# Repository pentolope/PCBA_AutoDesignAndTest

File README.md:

# pcbqa — board-agnostic KiCad / JLCPCB verification and release

A fail-closed validator that takes a native KiCad project plus a declarative
manifest and produces a machine-readable pass/fail matrix, generates the
fabrication outputs a release commit carries, and proves that a commit is one a
release tag may name.

**A release is a Git tag.**

- **commit** = the complete project state
- **committed fabrication artifacts** = the exact historical manufacturing
  outputs, kept as ordinary files so an old board can be refabricated years
  later without regenerating anything
- **Git tag** = the release identity
- **toolkit release gates** = engineering proof that the tagged state is
  acceptable

Git already provides immutable history, branches, diffs, rollback and exact
source identity. This toolkit does not reimplement any of that; it answers the
engineering question Git cannot: are these artifacts the ones this design
produces, and does this design pass.

KiCad is the sole design authority: nothing is believed because a report, a
label or a Python model says so. This repository contains no production board —
concrete designs appear only as isolated fixtures and examples.

Consume it from a board repository as a pinned Git submodule at
`tooling/PCBA_AutoDesignAndTest`. It carries one submodule of its own:
KiCad Routing Tools at `tooling/KiCadRoutingTools`, pinned to a commit on its
`pcba-autonomy` branch, so clone recursively.

## Commands

Ubuntu, and the system Python 3: the `kicad` package installs `pcbnew` into
this interpreter's `dist-packages` and `kicad-cli` onto PATH, and Shapely is
`python3-shapely`. See `docs/prerequisites.md`.

```bash
python3 run.py preflight
```
```bash
python3 run.py selftest
```
```bash
python3 run.py build <manifest.json>
```
```bash
python3 run.py validate <manifest.json> --write
```
```bash
python3 run.py check-board <manifest.json>
```
```bash
python3 run.py release-check <manifest.json>
```
```bash
python3 run.py gates
```
```bash
python3 run.py gates --missing <manifest.json>
```
```bash
python3 run.py fab refresh | select | impedance | export-stackup
```

`fab refresh` is the only command that may touch the network. It writes its
acquisition into a scratch directory in the committed catalog layout and
prints the semantic diff. After review, replace
`profiles/jlcpcb/catalog` with that scratch catalog as one exact set; do not
merge evidence directories. The commit is the approval and Git is the history.

`<manifest.json>` is a path. For this repository's own fixtures a bare name also
works — `portability`, `clean`, or a negative fixture's directory name.

`validate --only=` takes exact gate IDs, fnmatch patterns over them
(`ROUTE.*`), or a gate class — `design`, `release-artifact`, `fixture` — and a
partial run is always a diagnostic, never a verdict. The same selection is
available in-process as `pcbqa.gates.evaluate(manifest, only=..., 
board_path=...)`, where `board_path` substitutes a candidate board so a
routing search can be judged by the gates that will judge the release.

`check-board` is the sub-second integrity preflight: the tree's board is the
accepted routing candidate, the committed artifacts match the design as it
stands (naming which closure member moved when not), and no KiCad file the
design does not reach sits beside it. `gates --missing` lists every gate a
manifest has not enabled and the key that would enable it.

A manifest is validated against `schemas/manifest.v2.json` before any command
runs, and a key the toolkit does not implement is refused by name. Board-local
data belongs under `x_`-prefixed keys, permitted at every level;
`description`, `note`, `why` and `rationale` are annotation strings, also
permitted at every level.

## The release workflow

```text
develop on a branch
        ↓  run.py build          regenerate the fabrication outputs into the tree
        ↓  run.py validate -w    judge the design and those exact artifacts
        ↓  git commit            artifacts included; they are ordinary files
        ↓  run.py release-check  clean tree, exact submodules, gates pass now
        ↓  git tag -a            the release exists
```

A branch carries work in progress; a tag over a valid committed state is the
release.

`build` stages the design — the sources the manifest declares, the library
tables, and whatever those name inside the project — and runs KiCad against
that, never against the authoritative files. `pcb drc --refill-zones
--save-board`, which this validator requires because an export ships whatever
zone fill is stored, demonstrably rewrites the board. Every recursively
discovered project input must resolve inside the declared project root before
it can be staged. Outputs are installed into the paths the manifest declares,
all or nothing, together with `fabrication.json`: the digest of every artifact
and the source closure it came from.

`validate` exits nonzero on a blocking result. It is read-only unless `--write`
is given, so ordinary development validation never touches the working tree.

`release-check` writes nothing durable (its scratch run is discarded) and
changes no Git state. It exits zero only when
Git can say the tree is exactly the commit (submodules included), every release
artifact and every piece of required evidence is tracked, every mandatory gate
passes now, and the committed verdict is about this same design. Creating the
tag is a deliberate act and is left to the user.

To re-verify a historical release, check the tag out and run `release-check`
against it: the artifacts, the reports and the verdict are all in that commit,
and nothing has to be regenerated. Prefer annotated tags (`git tag -a`, or
`-s` to sign); protecting them from being moved or deleted is a property of the
remote — GitHub tag-protection rules, or `receive.denyDeleteTag` on a bare
repository — not something a validator can enforce locally.

Scratch for one invocation lives in `out/<board_id>/<run_id>/` and nothing
durable is kept there.

## Layout

| Path | Role |
|---|---|
| `pcbqa/core.py` | statuses, results, manifest, provenance, gate registry, reporting |
| `pcbqa/geom.py` | native pad/mask/via geometry via KiCad's own effective shapes |
| `pcbqa/gerber.py` | independent Gerber X2 + Excellon readers, incl. an aperture-macro interpreter |
| `pcbqa/canonical.py` | checkout-independent digests, driven by `.gitattributes` |
| `pcbqa/closure.py` | the source closure: what a result depends on |
| `pcbqa/claim.py` | one evidence model, and the conservative verdict rule |
| `pcbqa/sim/model_registry.py` | per-phenomenon simulation model evidence and coverage |
| `pcbqa/transmission_line.py` | manufacturer-independent closed forms |
| `pcbqa/build.py` | generating the fabrication outputs and installing them |
| `pcbqa/artifacts.py` | which committed files are the release artifact set |
| `pcbqa/release.py` | the Git preconditions of a release tag |
| `pcbqa/connectivity.py` | copper graph built from geometric intersection |
| `pcbqa/rules/` | reusable rule types: `NetTopologyRule`, `ConnectorContractRule`, `PlacementRule` |
| `pcbqa/gates/` | the gates themselves |
| `profiles/jlcpcb/` | substantiated JLCPCB capability and process data |
| `schemas/` | manifest and KiCad report schemas |
| `tests/manifests/` | manifests for this repository's own fixtures |
| `tests/fixtures/` | fixtures, including one curated negative integration fixture |
| `tests/paths.py` | where test assets live — one place, so fixtures can move |
| `tests/consumer.py` | optional external board for tests that need a real design |

## Scope: JLCPCB only

There is no multi-manufacturer abstraction and none is wanted. `profiles/jlcpcb/`
is organisation, not indirection.

A value only becomes a JLCPCB-wide requirement if it carries its provenance:
source, URL or document id, retrieval date, units, applicable service or
process, and any exceptions. A value is never promoted because one board happens
to use it — it is classified instead as configurable toolkit policy, a selected
board constraint, a conservative design target, or a board waiver, and left with
the board. The existing split between `via_mask.design_target_mm` (a board's
choice) and `via_mask.process.limit_mm` (a substantiated JLCPCB limit) is the
pattern to follow.

No live network lookup may change a validation or release result.
The committed `approved.json` and `catalog/evidence/` form an exact inventory:
every referenced file must exist and hash correctly, and any unreferenced entry
refuses catalog loading.

## Onboarding another board

Minimum manifest:

```json
{
  "schema_version": 2,
  "board_id": "my_board",
  "constraint_version": "v1",
  "project_root": "..",
  "tools": { "kicad_cli": "<path to kicad-cli>" },
  "sources": { "pcb": "my_board.kicad_pcb" },
  "board_origin_mm": [0.0, 0.0],
  "documentation_globs": [],
  "waivers": []
}
```

That alone runs the geometry-only gates. Every other gate stays
`NOT_APPLICABLE` **with a reason** until you add its policy block. Absence is
never a silent pass, and the gate still appears in the matrix.

Every limit a gate applies is a typed `Constraint` carrying its value, units
and manifest provenance. Gates compare through the constraint API; the toolkit
selftest performs a focused static audit of gate modules for policy-looking
literal comparisons that bypass it. Numeric constants intrinsic to algorithms
are marked with a rationale. This is repository-development enforcement, not a
consumer-board runtime gate.

## The generic/board split is enforced, not documented

`tests/test_suite.py::GenericSourceHygiene` extracts identifiers from every
manifest this repository ships — fixtures included — and fails if any appears in
`pcbqa/`, `schemas/` or `profiles/`. No board name is on its allowlist, and none
may be added.

Tests that need a real, released board take it from outside:

```bash
set PCBQA_CONSUMER_MANIFEST=<path to a board manifest>
```

With nothing set they skip, with a reason. That is how the toolkit keeps
coverage of installed-release behaviour without keeping a board.

## Fixtures are held to an exact inventory

`PROV.FIXTURE_INTEGRITY` requires every recorded file present and unchanged, and
every present file recorded. A stray `__pycache__` inside a fixture is therefore
a gate failure — do not run `compileall` over `tests/`.

`tests/fixtures/negative/microphone_array_reva/` is a curated real project that
is **intentionally defective**; the suite passes by proving the validator
rejects it. See its README before touching it.

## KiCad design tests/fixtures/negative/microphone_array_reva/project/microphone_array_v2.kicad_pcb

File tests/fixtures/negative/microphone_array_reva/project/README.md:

# 16-channel circular PDM microphone array

A 120 mm circular, four-layer KiCad 10 carrier for sixteen `MSM261DHP006` PDM
MEMS microphones running at 3.3 V. A socketed Sipeed Tang Nano 9K performs
acquisition and decimation; a 2012 Raspberry Pi Model B collects the audio over
SPI0 through a 26-way ribbon.

The sixteen acoustic ports sit on a 54.00 mm radius at 22.5 degree intervals,
channel 0 on +X, numbered counter-clockwise viewed from the component side.

## Design summary

| | |
|---|---|
| Board | 120 mm circle, 1.6 mm, 4 layers, ENIG, green / white |
| Stackup | signal / GND / GND / signal - both inner layers solid ground |
| Microphones | 16 x `MSM261DHP006`, top-ported, 3.3 V, ports up at the rim |
| Channel pairing | adjacent channels share a data line by clock edge, 8 data nets |
| Reference clock | 24.576 MHz oscillator to a global-clock FPGA pin |
| PDM clock | 3.072 MHz, buffered to 8 series-terminated branches |
| Sample rate | 48 kHz after decimate-by-64 |
| Level translation | none - microphones, FPGA banks and Pi GPIO are all 3.3 V |
| Power | Raspberry Pi 5 V only, via PTC and series Schottky |
| Microphone supply | `LP5907MFX-3.3`, 10 uVrms, 82 dB PSRR at 1 kHz |
| Host link | SPI0, 25 MHz design target, ESD-protected and series-damped |
| Assembly | all SMT on top; module sockets and Pi header hand-soldered |

The `MSM261DHP006` is a top-ported part, so "outward-facing" is realised as
ports facing up at the rim rather than radially. The capsules are
omnidirectional, so the array response is set by the port geometry, not by
package orientation; the alternative - sixteen perpendicular daughter-cards -
cannot be assembled by JLCPCB. This is discussed in
[docs/architecture.md](docs/architecture.md).

## Documentation

- [docs/architecture.md](docs/architecture.md) - signal, clock, power and
  stackup decisions, Tang Nano 9K pin assignments, and known limitations.
- [docs/host-interface.md](docs/host-interface.md) - Raspberry Pi pinout,
  bandwidth analysis and the wire protocol.
- [docs/routing.md](docs/routing.md) - what is pre-routed and why, and the
  microphone escape geometry.
- [docs/manufacturing.md](docs/manufacturing.md) - order options, order remark,
  microphone handling limits and bring-up sequence.
- [docs/sources.md](docs/sources.md) - every datasheet and manufacturer rule the
  design relies on, with the facts taken from each.

## Repository layout

| Path | Contents |
|---|---|
| `microphone_array_v2.kicad_sch` | generated schematic - do not hand-edit |
| `microphone_array_v2.kicad_pcb` | the board; no longer regenerated, see below |
| `microphone_array_v2.kicad_pro` | project settings, net classes, design rules |
| `MicArrayV2.kicad_sym` | generated project symbols |
| `MicArrayV2.pretty/` | project footprints: microphone, oscillator, silk-free probe pads |
| `constraints.json` | frozen requirements and manufacturing profile |
| `tools/` | design source of truth, generators and checkers |
| `docs/` | engineering documentation |
| `generated/` | reports, renders and release artefacts |

## Source of truth

`tools/netlist.py` holds the complete component list, netlist and placement.
The schematic is generated from it. The board was too, until the host block was
finished with an external autorouter; it is now edited in place by
`tools/patch_board.py`, `tools/cleanup_tracks.py` and
`tools/place_testpoints.py`, each of which records what it did. Three
independent gates keep schematic and board in step:

- `tools/check_netlist_parity.py` extracts the netlist from the generated
  schematic with `kicad-cli` and compares it against `netlist.py`, including an
  exact match on which pins are deliberately left unconnected.
- KiCad's `--schematic-parity` DRC compares the board against the schematic.
- `tools/check_placement.py` re-derives the array geometry from the board:
  every microphone's acoustic port radius and azimuth, every Tang Nano 9K
  socket pin coordinate, courtyard overlaps by exact polygon distance, JLCPCB
  package-pair body spacing, and edge clearance.

`tools/check_routes.py` adds the post-route constraints KiCad cannot express:
allowed layers per net, via budgets on the clock nets, branch length matching
across the eight microphone pairs, different-net crossings, and acid traps -
corners left with an interior angle under 90 degrees.

Regeneration commands are in [docs/manufacturing.md](docs/manufacturing.md).

## Status

**Fully routed and DRC clean.** KiCad reports 0 DRC violations, 0 unconnected
items and 0 schematic parity issues; ERC, netlist parity and the placement audit
all pass. The eight PDM clock branches keep their intended topology — F.Cu only,
zero vias, length-matched to 21.5 mm — and both inner layers are still solid
ground.

Two hard shorts found after routing (the regulator's enable pin and the 5 V
input lane, both tied to ground by misplaced stitching vias) have been repaired
by [tools/patch_board.py](tools/patch_board.py).

The copper has been through a cleanup pass ([tools/cleanup_tracks.py](tools/cleanup_tracks.py)):
no segment is under 0.05 mm and no corner is left with an interior angle under
90°, so there are no acid traps. Fourteen of the twenty-four test points are
back, each placed on top of a piece of its own net so it needs no track of its
own; the other ten have nowhere on the top layer to go, and are listed in
[docs/status.md](docs/status.md).

The board is no longer regenerated by `tools/gen_pcb.py`.

A release package is sealed at `generated/release/` — Gerbers, drills, BOM, CPL,
schematic PDF and a SHA-256 manifest, all built from one board revision in a
single run. It is a release *candidate*: JLCPCB's own part orientations cannot
be checked locally, so step through their previews before ordering. See
[docs/manufacturing.md](docs/manufacturing.md).

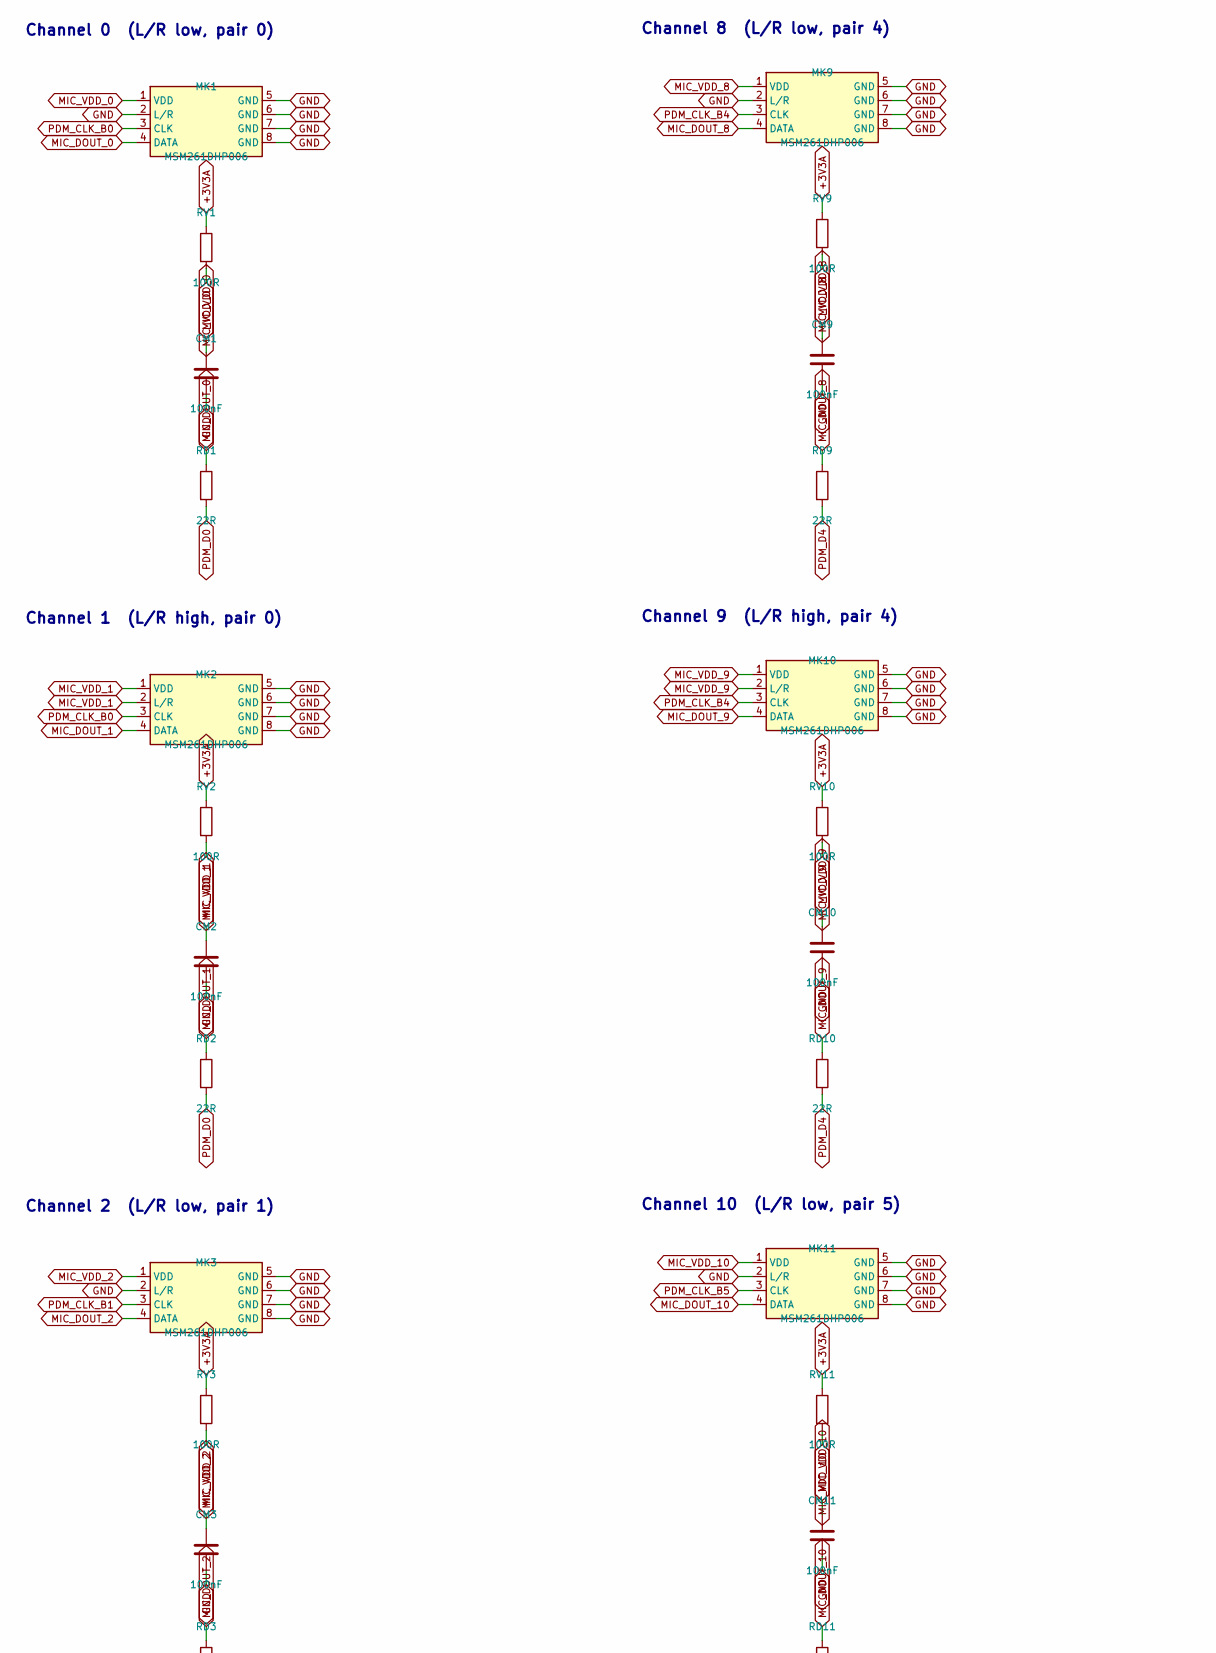
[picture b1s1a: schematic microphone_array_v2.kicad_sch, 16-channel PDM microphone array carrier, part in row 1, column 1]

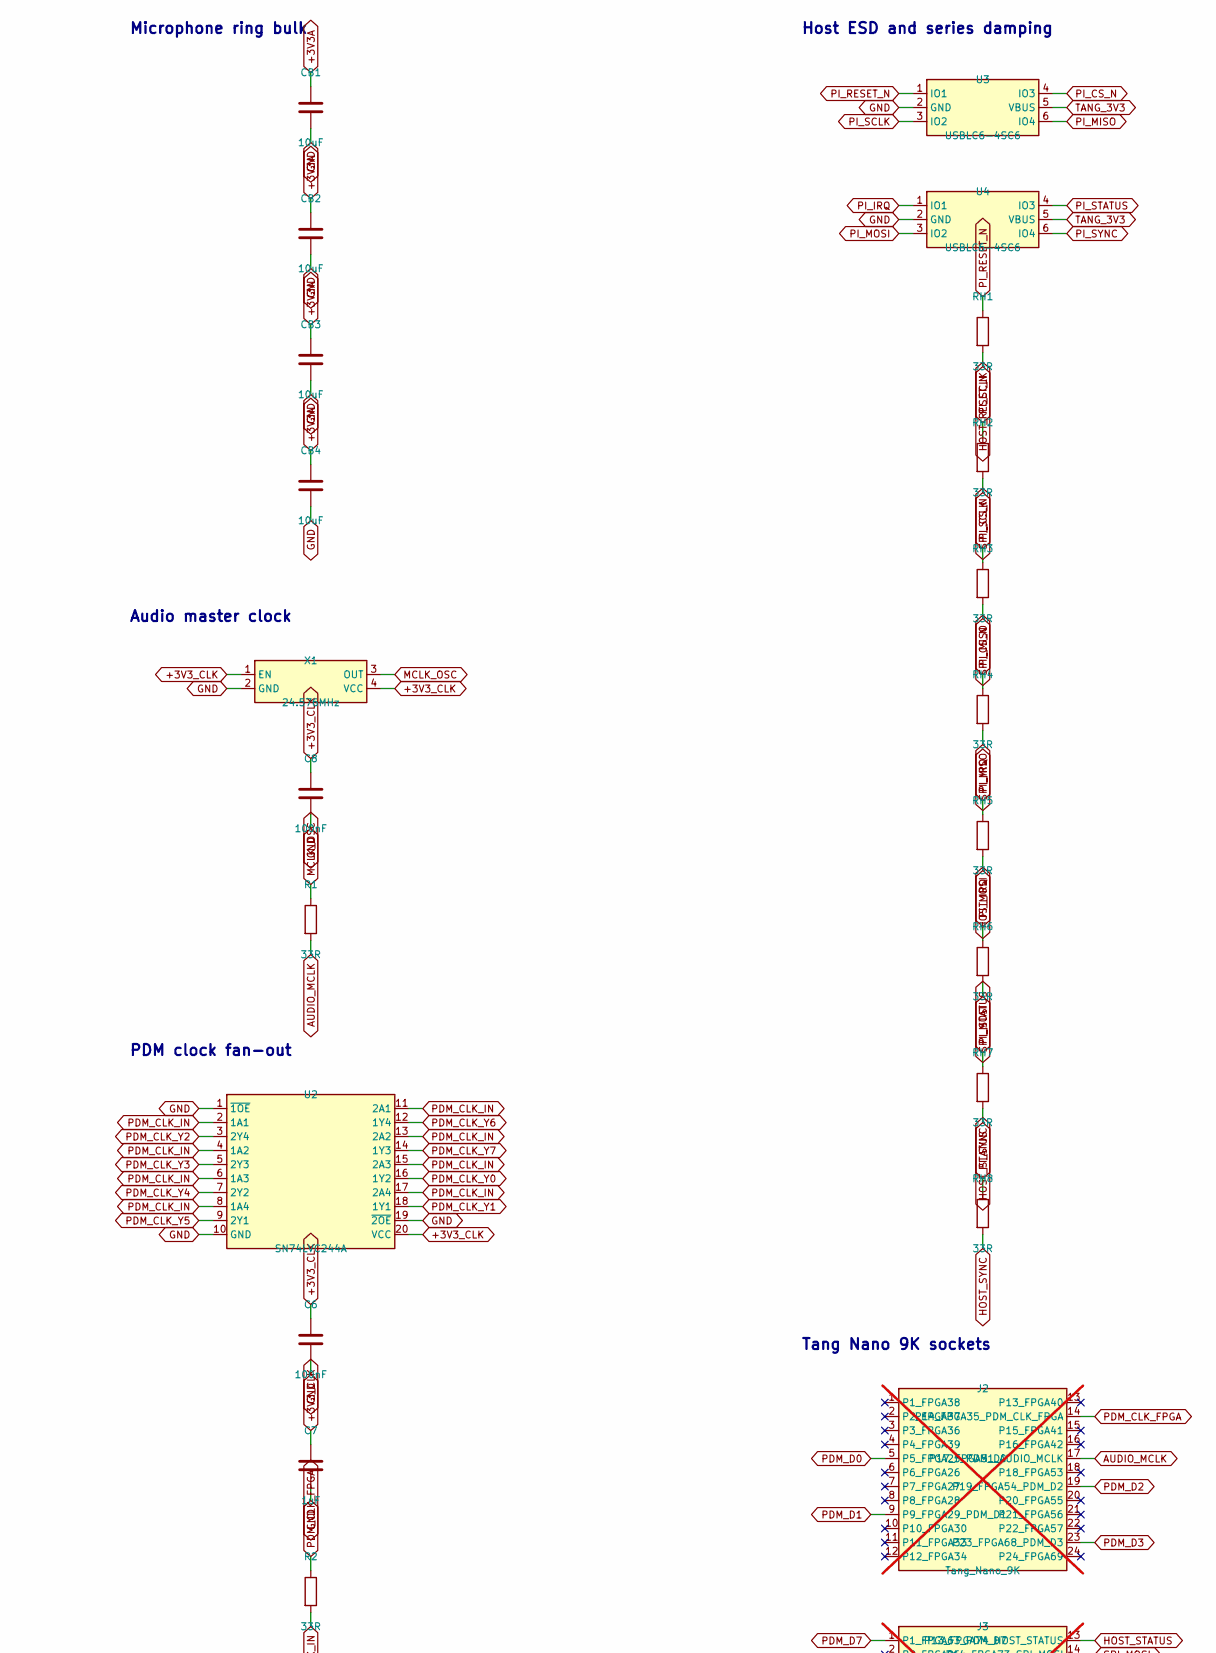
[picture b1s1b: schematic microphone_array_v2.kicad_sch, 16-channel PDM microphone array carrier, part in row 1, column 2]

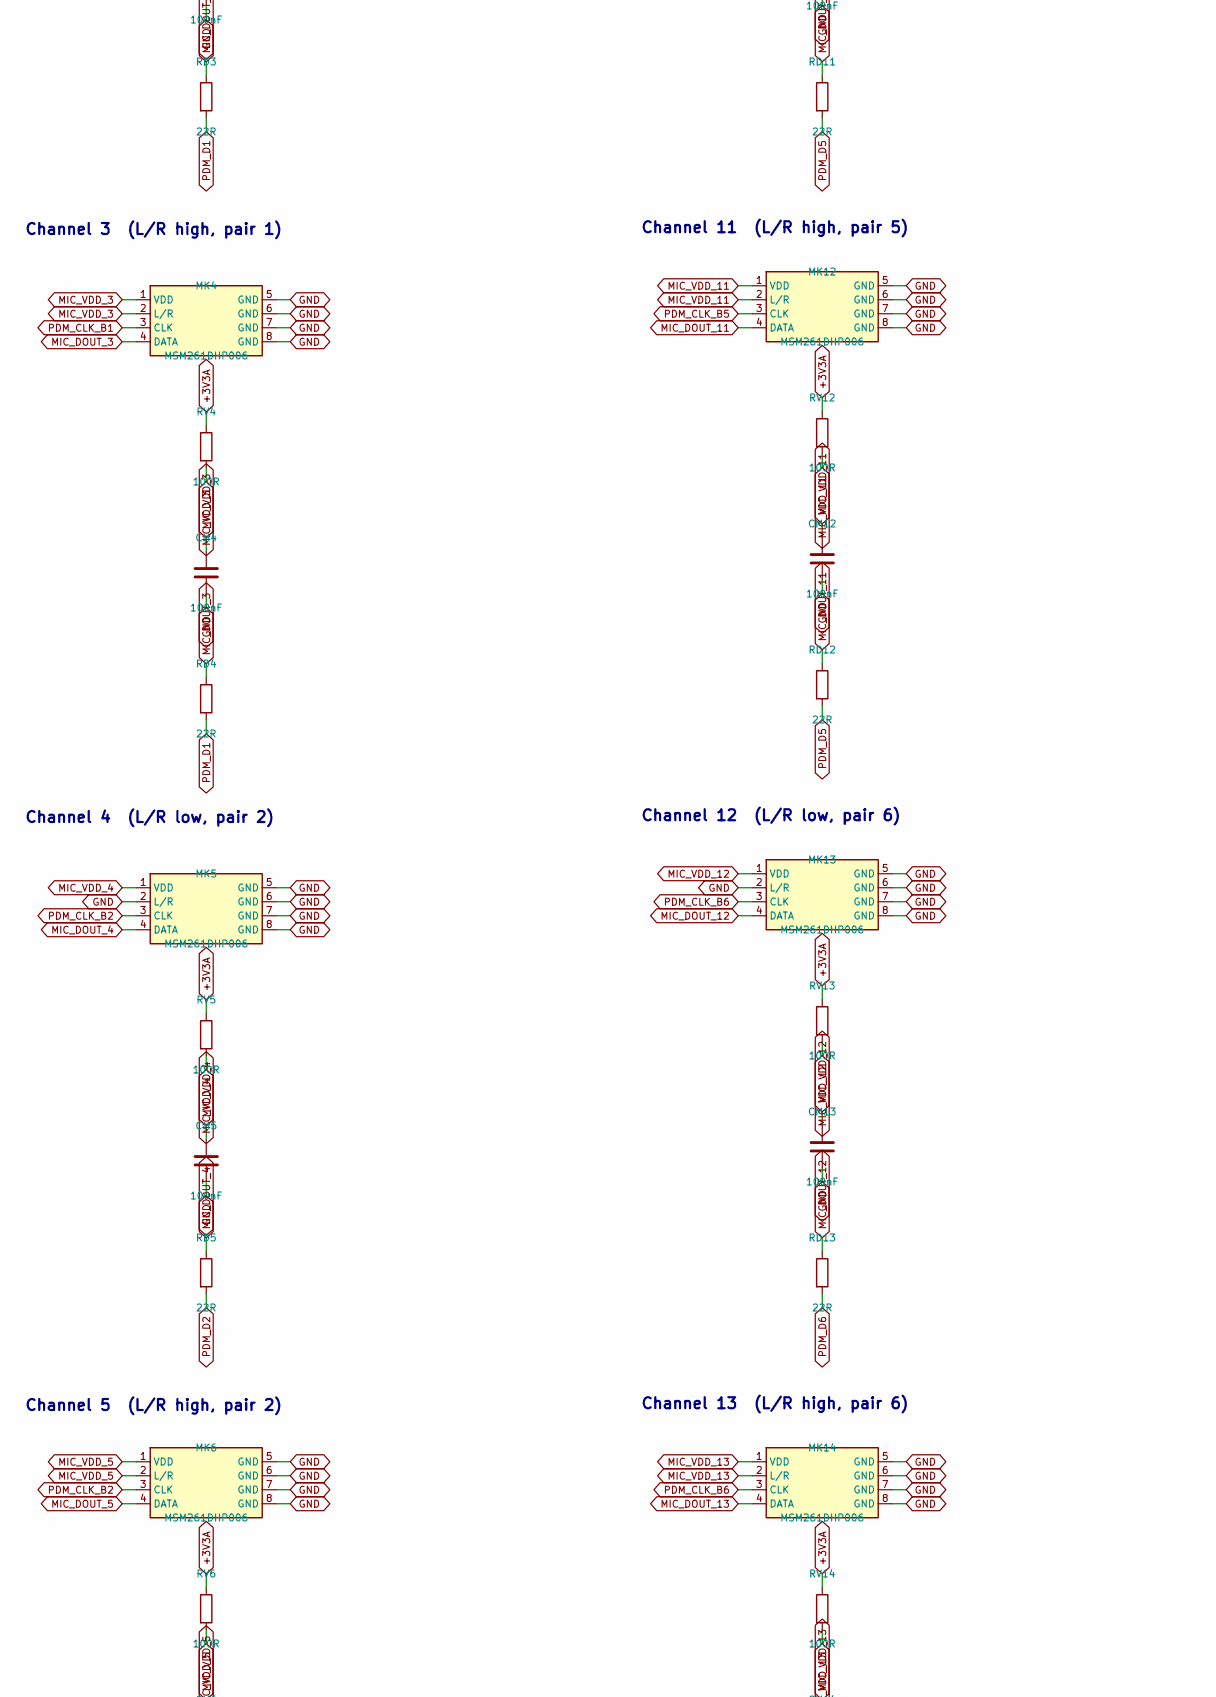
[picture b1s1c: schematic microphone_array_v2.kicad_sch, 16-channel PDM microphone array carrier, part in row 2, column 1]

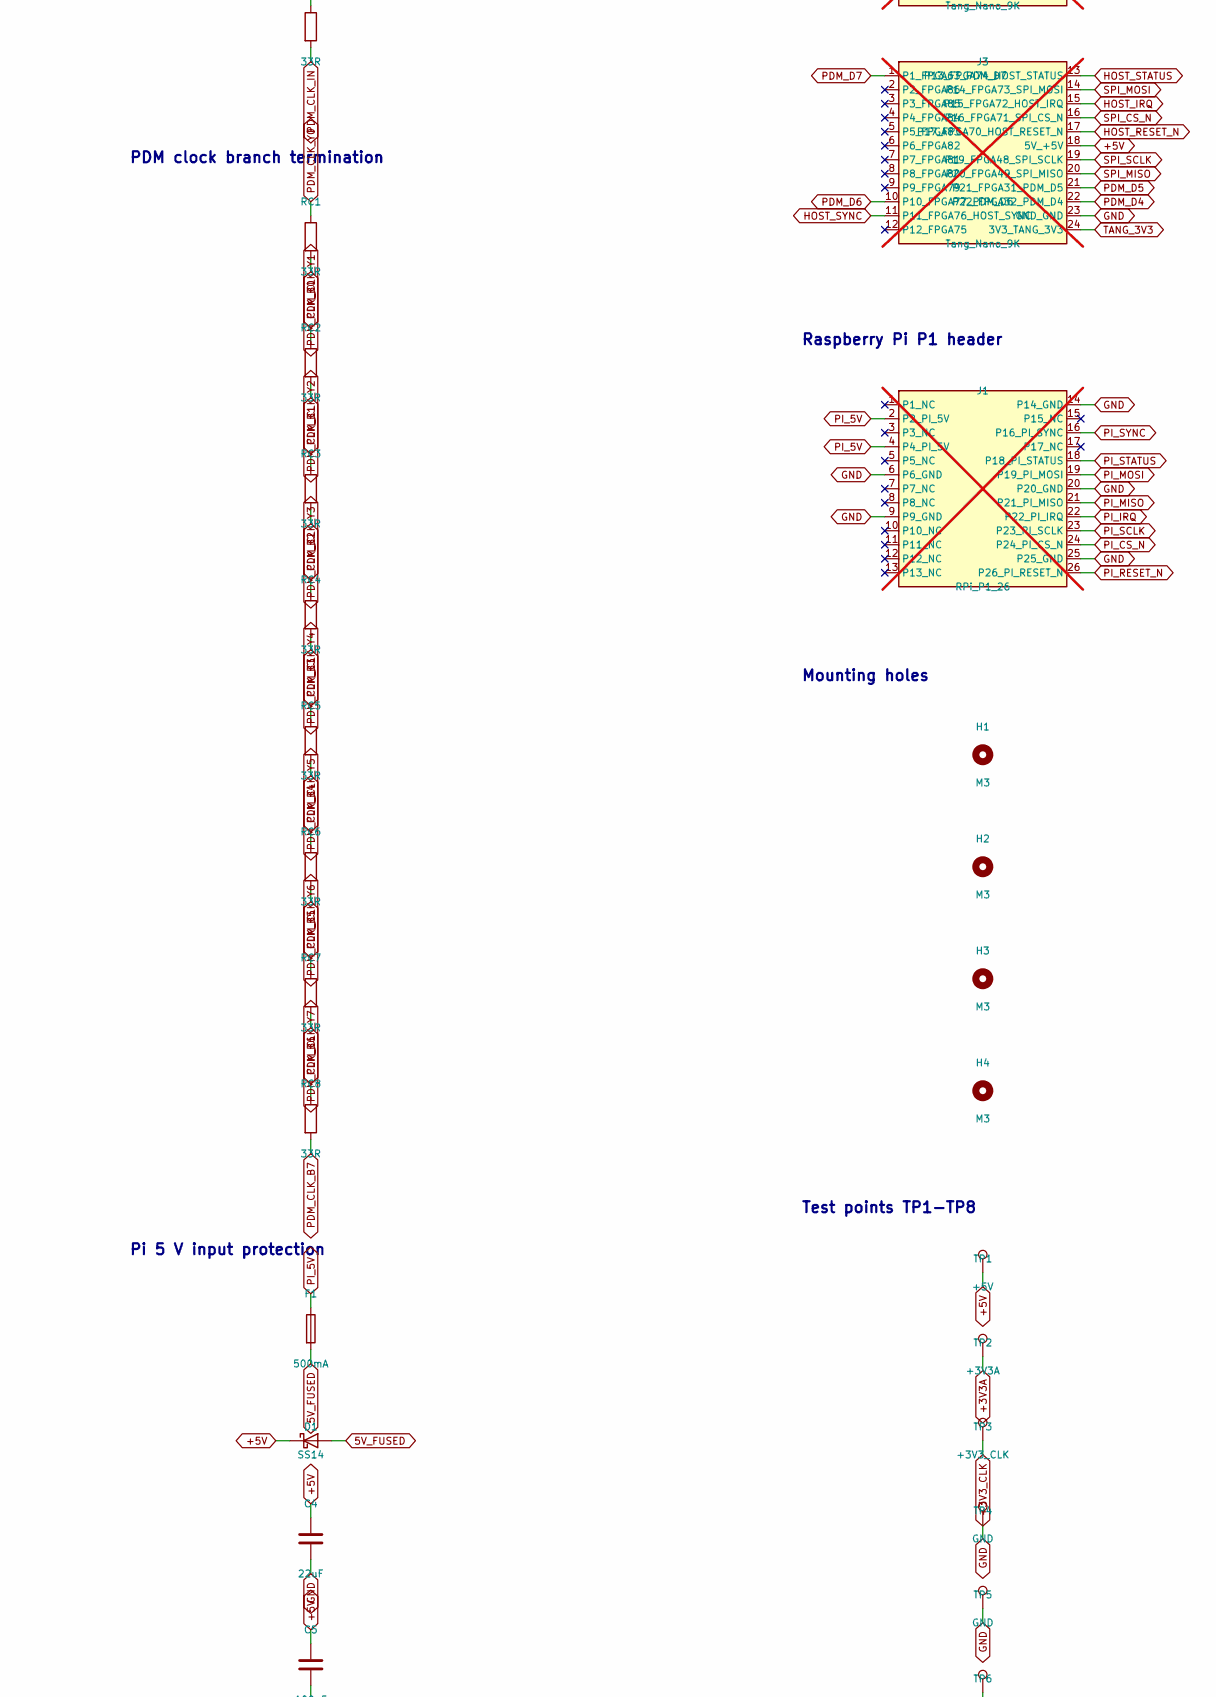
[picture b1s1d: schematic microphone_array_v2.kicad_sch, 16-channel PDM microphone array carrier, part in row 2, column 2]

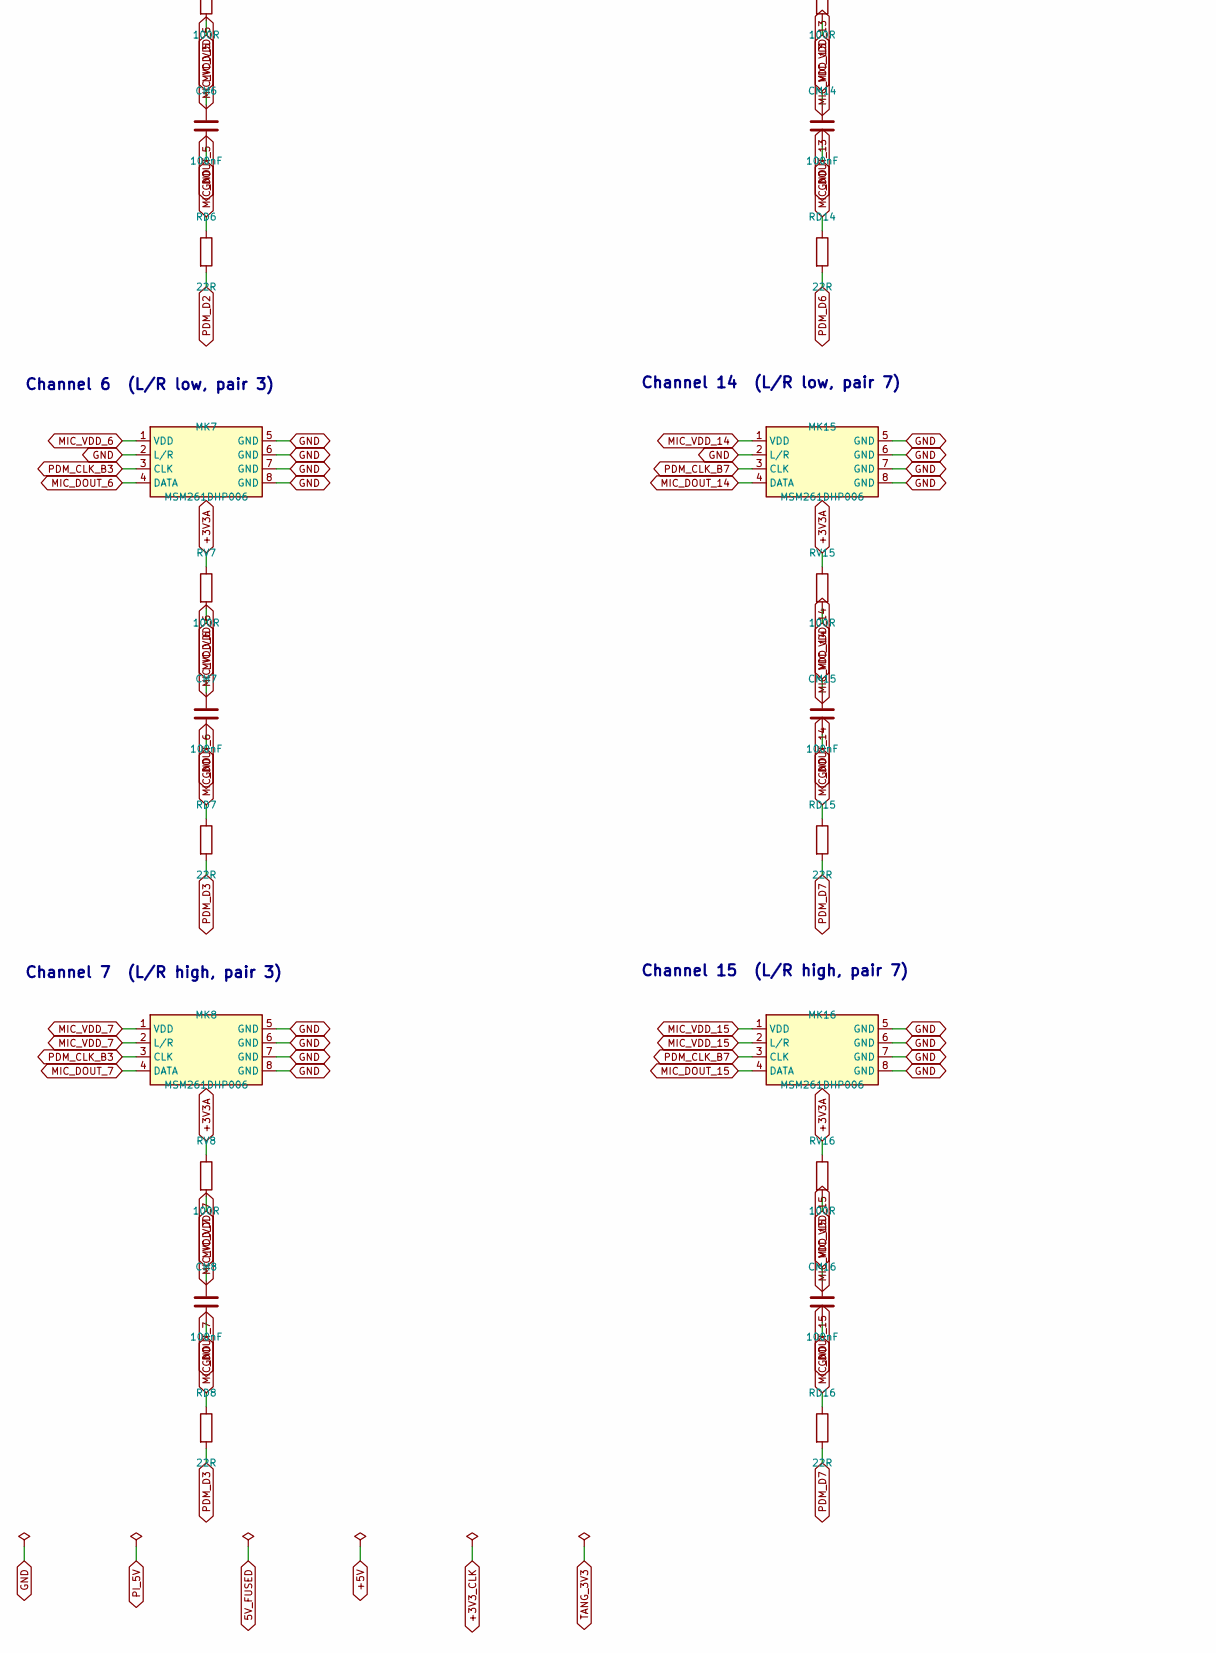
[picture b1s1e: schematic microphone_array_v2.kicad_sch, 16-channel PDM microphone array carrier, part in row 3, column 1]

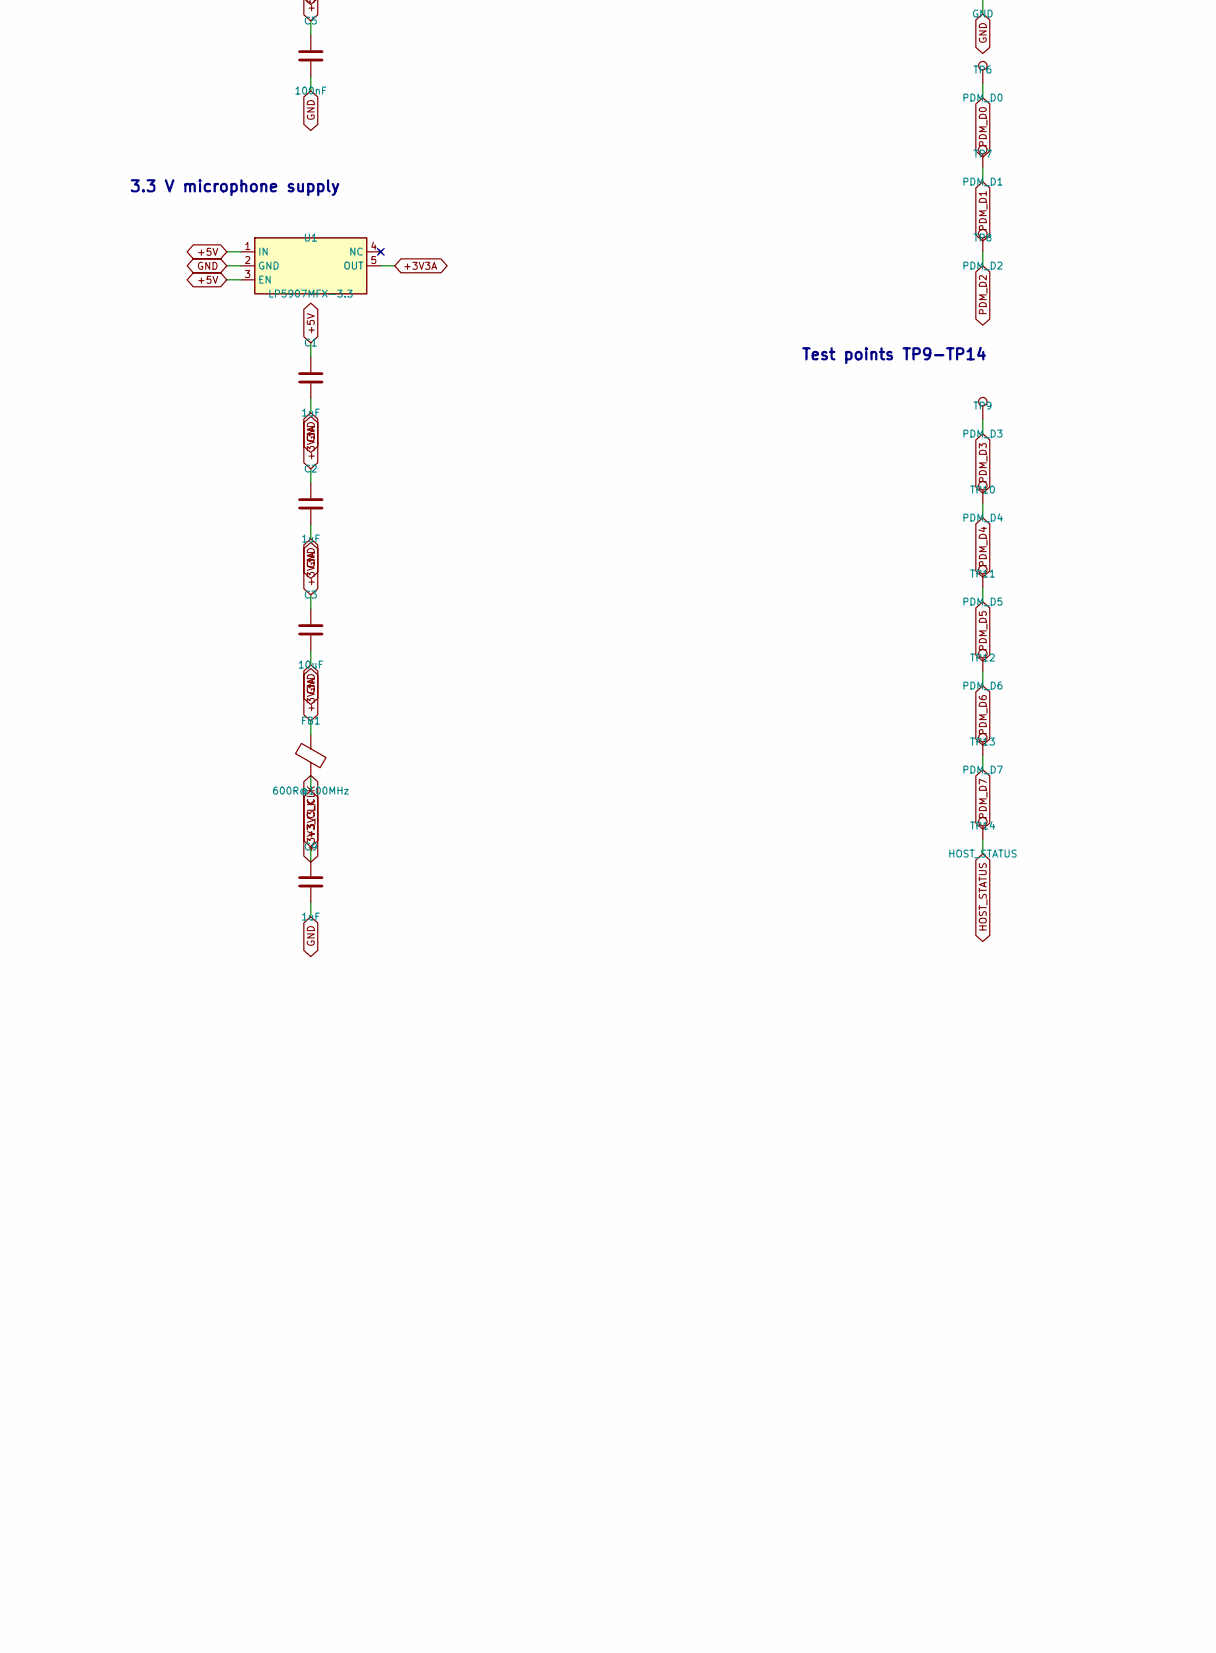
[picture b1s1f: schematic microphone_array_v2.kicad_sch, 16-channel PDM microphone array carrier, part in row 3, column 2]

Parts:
C1, C2, C7, C9: 1uF; C_0603_1608Metric; MPN CC0603KRX7R8BB105; LCSC C106858
C3: 10uF; C_0805_2012Metric; MPN CL21A106KAYNNNE; LCSC C15850
C4: 22uF; C_0805_2012Metric; MPN C2012X5R1C226KT000E; LCSC C76637
C5, C6, C8: 100nF; C_0402_1005Metric; MPN CL05B104KO5NNNC; LCSC C1525
CB1, CB2, CB3, CB4: 10uF; C_0805_2012Metric; MPN CL21A106KAYNNNE; LCSC C15850
CM1, CM2, CM3, CM4, CM5, CM6, CM7, CM8, CM9, CM10, CM11, CM12, CM13, CM14, CM15, CM16: 100nF; C_0402_1005Metric; MPN CL05B104KO5NNNC; LCSC C1525
D1: SS14; D_SMA; MPN SS14; LCSC C2480
F1: 500mA; Fuse_1812_4532Metric; MPN JK-MSMD050-30; LCSC C369168
FB1: 600R@100MHz; L_0805_2012Metric; MPN GZ2012D601TF; LCSC C1017
H1, H2, H3, H4: M3; MountingHole_3.2mm_M3
J1: RPi_P1_26; PinHeader_2x13_P2.54mm_Vertical; not fitted
J2, J3: Tang_Nano_9K; PinHeader_1x24_P2.54mm_Vertical; not fitted
MK1, MK2, MK3, MK4, MK5, MK6, MK7, MK8, MK9, MK10, MK11, MK12, MK13, MK14, MK15, MK16: MSM261DHP006; MSM261DHP006_LGA-8_3x4mm_TopPort; MPN MSM261DHP006; LCSC C22390138
R1, R2: 33R; R_0402_1005Metric; MPN 0402WGF330JTCE; LCSC C25105
RC1, RC2, RC3, RC4, RC5, RC6, RC7, RC8: 33R; R_0402_1005Metric; MPN 0402WGF330JTCE; LCSC C25105
RD1, RD2, RD3, RD4, RD5, RD6, RD7, RD8, RD9, RD10, RD11, RD12, RD13, RD14, RD15, RD16: 22R; R_0402_1005Metric; MPN 0402WGF220JTCE; LCSC C25092
RH1, RH2, RH3, RH4, RH5, RH6, RH7, RH8: 33R; R_0402_1005Metric; MPN 0402WGF330JTCE; LCSC C25105
RV1, RV2, RV3, RV4, RV5, RV6, RV7, RV8, RV9, RV10, RV11, RV12, RV13, RV14, RV15, RV16: 100R; R_0402_1005Metric; MPN 0402WGF1000TCE; LCSC C25076
TP1: +5V; TestPoint_Pad_D1.0mm_NoSilk
TP2: +3V3A; TestPoint_Pad_D1.5mm_NoSilk
TP3: +3V3_CLK; TestPoint_Pad_D1.5mm_NoSilk
TP4, TP5: GND; TestPoint_Pad_D1.5mm_NoSilk
TP6: PDM_D0; TestPoint_Pad_D1.5mm_NoSilk
TP7: PDM_D1; TestPoint_Pad_D1.5mm_NoSilk
TP8: PDM_D2; TestPoint_Pad_D1.5mm_NoSilk
TP9: PDM_D3; TestPoint_Pad_D1.5mm_NoSilk
TP10: PDM_D4; TestPoint_Pad_D1.5mm_NoSilk
TP11: PDM_D5; TestPoint_Pad_D1.5mm_NoSilk
TP12: PDM_D6; TestPoint_Pad_D1.5mm_NoSilk
TP13: PDM_D7; TestPoint_Pad_D1.5mm_NoSilk
TP14: HOST_STATUS; TestPoint_Pad_D1.0mm_NoSilk
U1: LP5907MFX-3.3; SOT-23-5; MPN LP5907MFX-3.3/NOPB; LCSC C80670
U2: SN74LVC244A; TSSOP-20_4.4x6.5mm_P0.65mm; MPN SN74LVC244APWR; LCSC C7668
U3, U4: USBLC6-4SC6; SOT-23-6; MPN USBLC6-4SC6; LCSC C111212
X1: 24.576MHz; Oscillator_SMD_YXC_3.2x2.5mm_4Pin; MPN OT322524.576MJBA4SL; LCSC C2831388

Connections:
5V_FUSED: D1.2 (A), F1.2
+3V3A: C2.1, C3.1, CB1.1, CB2.1, CB3.1, CB4.1, FB1.1, RV1.1, RV2.1, RV3.1, RV4.1, RV5.1, RV6.1, RV7.1, RV8.1, RV9.1, RV10.1, RV11.1, RV12.1, RV13.1, RV14.1, RV15.1, RV16.1, TP2.1, U1.5 (OUT)
+3V3_CLK: C6.1, C7.1, C8.1, C9.1, FB1.2, TP3.1, U2.20 (VCC), X1.1 (EN), X1.4 (VCC)
+5V: C1.1, C4.1, C5.1, D1.1 (K), J3.18 (5V_+5V), TP1.1, U1.1 (IN), U1.3 (EN)
AUDIO_MCLK: J2.17 (P17_FPGA51_AUDIO_MCLK), R1.2
GND: C1.2, C2.2, C3.2, C4.2, C5.2, C6.2, C7.2, C8.2, C9.2, CB1.2, CB2.2, CB3.2, CB4.2, CM1.2, CM2.2, CM3.2, CM4.2, CM5.2, CM6.2, CM7.2, CM8.2, CM9.2, CM10.2, CM11.2, CM12.2, CM13.2, CM14.2, CM15.2, CM16.2, J1.6 (P6_GND), J1.9 (P9_GND), J1.14 (P14_GND), J1.20 (P20_GND), J1.25 (P25_GND), J3.23 (GND_GND), MK1.2 (L/R), MK1.5 (GND), MK1.6 (GND), MK1.7 (GND), MK1.8 (GND), MK2.5 (GND), MK2.6 (GND), MK2.7 (GND), MK2.8 (GND), MK3.2 (L/R), MK3.5 (GND), MK3.6 (GND), MK3.7 (GND), MK3.8 (GND), MK4.5 (GND), MK4.6 (GND), MK4.7 (GND), MK4.8 (GND), MK5.2 (L/R), MK5.5 (GND), MK5.6 (GND), MK5.7 (GND), MK5.8 (GND), MK6.5 (GND), MK6.6 (GND), MK6.7 (GND), MK6.8 (GND), MK7.2 (L/R), MK7.5 (GND), MK7.6 (GND), MK7.7 (GND), MK7.8 (GND), MK8.5 (GND), MK8.6 (GND), MK8.7 (GND), MK8.8 (GND), MK9.2 (L/R), MK9.5 (GND), MK9.6 (GND), MK9.7 (GND), MK9.8 (GND), MK10.5 (GND), MK10.6 (GND), MK10.7 (GND), MK10.8 (GND), MK11.2 (L/R), MK11.5 (GND), MK11.6 (GND), MK11.7 (GND), MK11.8 (GND), MK12.5 (GND), MK12.6 (GND), MK12.7 (GND), MK12.8 (GND), MK13.2 (L/R), MK13.5 (GND), MK13.6 (GND), MK13.7 (GND), MK13.8 (GND), MK14.5 (GND), MK14.6 (GND), MK14.7 (GND), MK14.8 (GND), MK15.2 (L/R), MK15.5 (GND), MK15.6 (GND), MK15.7 (GND), MK15.8 (GND), MK16.5 (GND), MK16.6 (GND), MK16.7 (GND), MK16.8 (GND), TP4.1, TP5.1, U1.2 (GND), U2.1 (~1OE), U2.10 (GND), U2.19 (~2OE), U3.2 (GND), U4.2 (GND), X1.2 (GND)
HOST_IRQ: J3.15 (P15_FPGA72_HOST_IRQ), RH5.2
HOST_RESET_N: J3.17 (P17_FPGA70_HOST_RESET_N), RH1.2
HOST_STATUS: J3.13 (P13_FPGA74_HOST_STATUS), RH7.2, TP14.1
HOST_SYNC: J3.11 (P11_FPGA76_HOST_SYNC), RH8.2
MCLK_OSC: R1.1, X1.3 (OUT)
MIC_DOUT_0: MK1.4 (DATA), RD1.1
MIC_DOUT_1: MK2.4 (DATA), RD2.1
MIC_DOUT_2: MK3.4 (DATA), RD3.1
MIC_DOUT_3: MK4.4 (DATA), RD4.1
MIC_DOUT_4: MK5.4 (DATA), RD5.1
MIC_DOUT_5: MK6.4 (DATA), RD6.1
MIC_DOUT_6: MK7.4 (DATA), RD7.1
MIC_DOUT_7: MK8.4 (DATA), RD8.1
MIC_DOUT_8: MK9.4 (DATA), RD9.1
MIC_DOUT_9: MK10.4 (DATA), RD10.1
MIC_DOUT_10: MK11.4 (DATA), RD11.1
MIC_DOUT_11: MK12.4 (DATA), RD12.1
MIC_DOUT_12: MK13.4 (DATA), RD13.1
MIC_DOUT_13: MK14.4 (DATA), RD14.1
MIC_DOUT_14: MK15.4 (DATA), RD15.1
MIC_DOUT_15: MK16.4 (DATA), RD16.1
MIC_VDD_0: CM1.1, MK1.1 (VDD), RV1.2
MIC_VDD_1: CM2.1, MK2.1 (VDD), MK2.2 (L/R), RV2.2
MIC_VDD_2: CM3.1, MK3.1 (VDD), RV3.2
MIC_VDD_3: CM4.1, MK4.1 (VDD), MK4.2 (L/R), RV4.2
MIC_VDD_4: CM5.1, MK5.1 (VDD), RV5.2
MIC_VDD_5: CM6.1, MK6.1 (VDD), MK6.2 (L/R), RV6.2
MIC_VDD_6: CM7.1, MK7.1 (VDD), RV7.2
MIC_VDD_7: CM8.1, MK8.1 (VDD), MK8.2 (L/R), RV8.2
MIC_VDD_8: CM9.1, MK9.1 (VDD), RV9.2
MIC_VDD_9: CM10.1, MK10.1 (VDD), MK10.2 (L/R), RV10.2
MIC_VDD_10: CM11.1, MK11.1 (VDD), RV11.2
MIC_VDD_11: CM12.1, MK12.1 (VDD), MK12.2 (L/R), RV12.2
MIC_VDD_12: CM13.1, MK13.1 (VDD), RV13.2
MIC_VDD_13: CM14.1, MK14.1 (VDD), MK14.2 (L/R), RV14.2
MIC_VDD_14: CM15.1, MK15.1 (VDD), RV15.2
MIC_VDD_15: CM16.1, MK16.1 (VDD), MK16.2 (L/R), RV16.2
PDM_CLK_B0: MK1.3 (CLK), MK2.3 (CLK), RC1.2
PDM_CLK_B1: MK3.3 (CLK), MK4.3 (CLK), RC2.2
PDM_CLK_B2: MK5.3 (CLK), MK6.3 (CLK), RC3.2
PDM_CLK_B3: MK7.3 (CLK), MK8.3 (CLK), RC4.2
PDM_CLK_B4: MK9.3 (CLK), MK10.3 (CLK), RC5.2
PDM_CLK_B5: MK11.3 (CLK), MK12.3 (CLK), RC6.2
PDM_CLK_B6: MK13.3 (CLK), MK14.3 (CLK), RC7.2
PDM_CLK_B7: MK15.3 (CLK), MK16.3 (CLK), RC8.2
PDM_CLK_FPGA: J2.14 (P14_FPGA35_PDM_CLK_FPGA), R2.1
PDM_CLK_IN: R2.2, U2.2 (1A1), U2.4 (1A2), U2.6 (1A3), U2.8 (1A4), U2.11 (2A1), U2.13 (2A2), U2.15 (2A3), U2.17 (2A4)
PDM_CLK_Y0: RC1.1, U2.16 (1Y2)
PDM_CLK_Y1: RC2.1, U2.18 (1Y1)
PDM_CLK_Y2: RC3.1, U2.3 (2Y4)
PDM_CLK_Y3: RC4.1, U2.5 (2Y3)
PDM_CLK_Y4: RC5.1, U2.7 (2Y2)
PDM_CLK_Y5: RC6.1, U2.9 (2Y1)
PDM_CLK_Y6: RC7.1, U2.12 (1Y4)
PDM_CLK_Y7: RC8.1, U2.14 (1Y3)
PDM_D0: J2.5 (P5_FPGA25_PDM_D0), RD1.2, RD2.2, TP6.1
PDM_D1: J2.9 (P9_FPGA29_PDM_D1), RD3.2, RD4.2, TP7.1
PDM_D2: J2.19 (P19_FPGA54_PDM_D2), RD5.2, RD6.2, TP8.1
PDM_D3: J2.23 (P23_FPGA68_PDM_D3), RD7.2, RD8.2, TP9.1
PDM_D4: J3.22 (P22_FPGA32_PDM_D4), RD9.2, RD10.2, TP10.1
PDM_D5: J3.21 (P21_FPGA31_PDM_D5), RD11.2, RD12.2, TP11.1
PDM_D6: J3.10 (P10_FPGA77_PDM_D6), RD13.2, RD14.2, TP12.1
PDM_D7: J3.1 (P1_FPGA63_PDM_D7), RD15.2, RD16.2, TP13.1
PI_5V: F1.1, J1.2 (P2_PI_5V), J1.4 (P4_PI_5V)
PI_CS_N: J1.24 (P24_PI_CS_N), RH3.1, U3.4 (IO3)
PI_IRQ: J1.22 (P22_PI_IRQ), RH5.1, U4.1 (IO1)
PI_MISO: J1.21 (P21_PI_MISO), RH4.1, U3.6 (IO4)
PI_MOSI: J1.19 (P19_PI_MOSI), RH6.1, U4.3 (IO2)
PI_RESET_N: J1.26 (P26_PI_RESET_N), RH1.1, U3.1 (IO1)
PI_SCLK: J1.23 (P23_PI_SCLK), RH2.1, U3.3 (IO2)
PI_STATUS: J1.18 (P18_PI_STATUS), RH7.1, U4.4 (IO3)
PI_SYNC: J1.16 (P16_PI_SYNC), RH8.1, U4.6 (IO4)
SPI_CS_N: J3.16 (P16_FPGA71_SPI_CS_N), RH3.2
SPI_MISO: J3.20 (P20_FPGA49_SPI_MISO), RH4.2
SPI_MOSI: J3.14 (P14_FPGA73_SPI_MOSI), RH6.2
SPI_SCLK: J3.19 (P19_FPGA48_SPI_SCLK), RH2.2
TANG_3V3: J3.24 (3V3_TANG_3V3), U3.5 (VBUS), U4.5 (VBUS)

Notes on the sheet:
Channel 0 (L/R low, pair 0)
Channel 1 (L/R high, pair 0)
Channel 2 (L/R low, pair 1)
Channel 3 (L/R high, pair 1)
Channel 4 (L/R low, pair 2)
Channel 5 (L/R high, pair 2)
Channel 6 (L/R low, pair 3)
Channel 7 (L/R high, pair 3)
Channel 8 (L/R low, pair 4)
Channel 9 (L/R high, pair 4)
Channel 10 (L/R low, pair 5)
Channel 11 (L/R high, pair 5)
Channel 12 (L/R low, pair 6)
Channel 13 (L/R high, pair 6)
Channel 14 (L/R low, pair 7)
Channel 15 (L/R high, pair 7)
Microphone ring bulk
Audio master clock
PDM clock fan-out
PDM clock branch termination
Pi 5 V input protection
3.3 V microphone supply
Host ESD and series damping
Tang Nano 9K sockets
Raspberry Pi P1 header
Mounting holes
Test points TP1-TP8
Test points TP9-TP14
